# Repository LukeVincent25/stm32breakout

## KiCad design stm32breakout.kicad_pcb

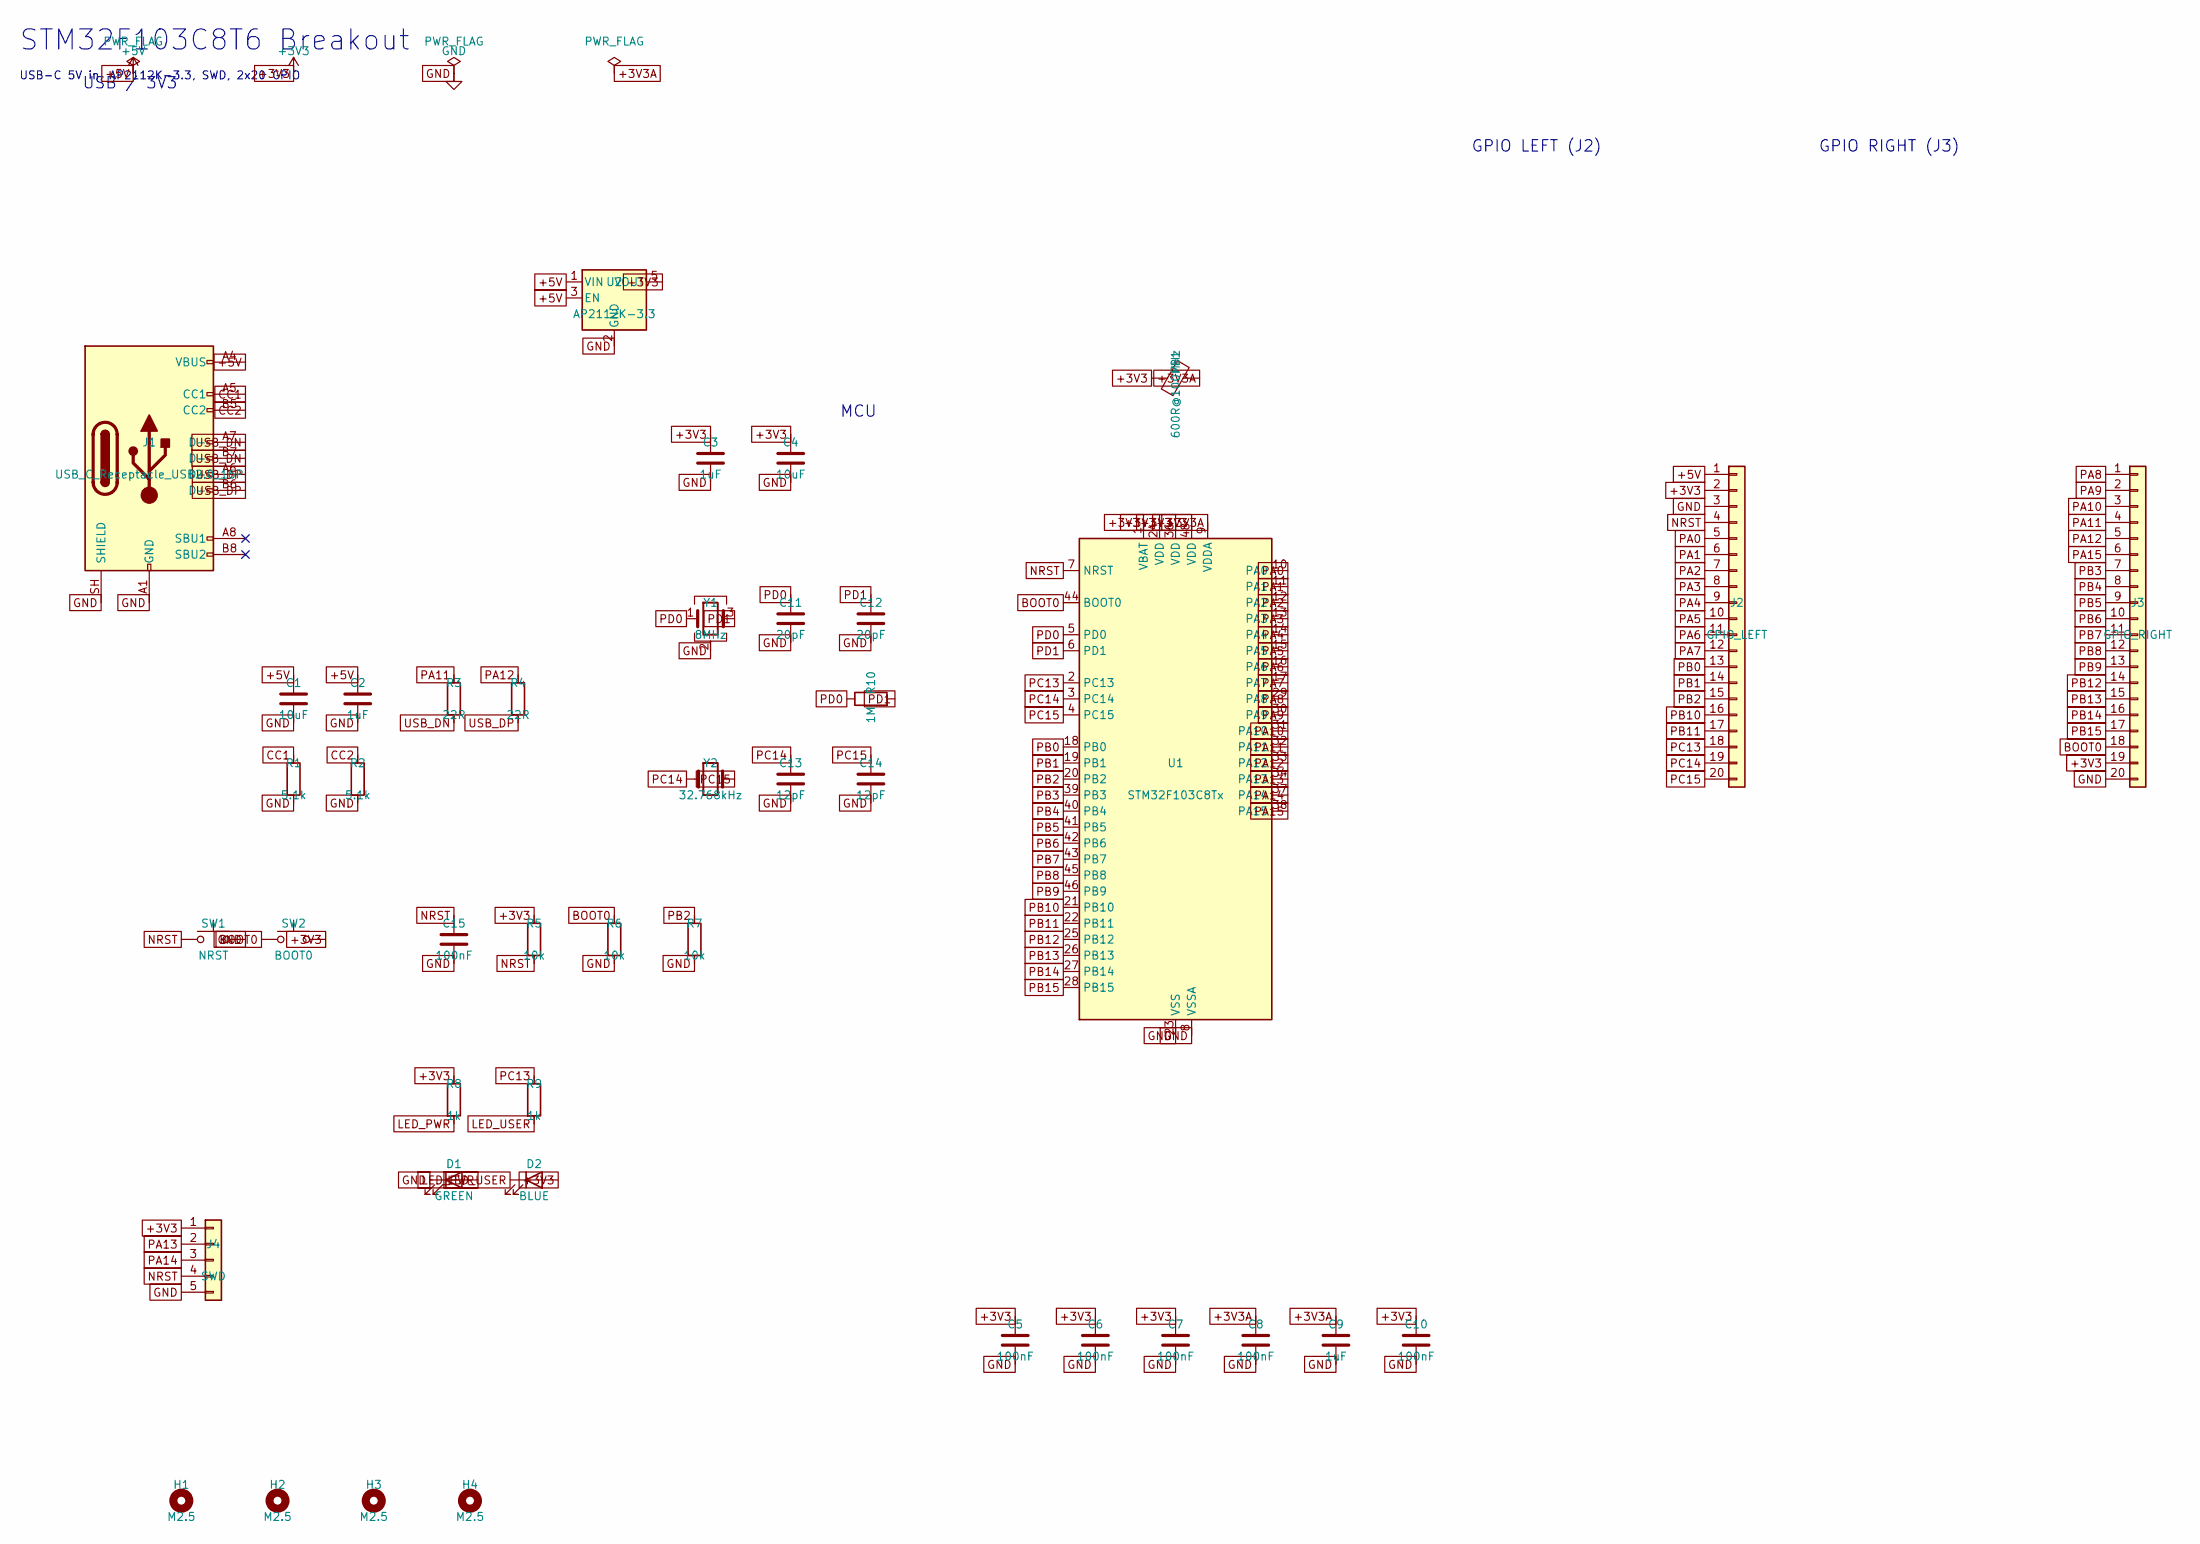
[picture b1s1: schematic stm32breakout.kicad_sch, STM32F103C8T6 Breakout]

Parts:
C1, C4: 10uF; C_0805_2012Metric; LCSC C19702
C2, C3, C9: 1uF; C_0603_1608Metric; LCSC C15849
C5, C6, C7, C8, C10, C15: 100nF; C_0603_1608Metric; LCSC C14663
C11, C12: 20pF; C_0603_1608Metric; LCSC C1645
C13, C14: 12pF; C_0603_1608Metric; LCSC C1647
D1: GREEN; LED_0603_1608Metric; LCSC C72043
D2: BLUE; LED_0603_1608Metric; LCSC C72041
FB1: 600R@100MHz; L_0603_1608Metric; LCSC C23611
H1, H2, H3, H4: M2.5; MountingHole_2.7mm_M2.5
J1: USB_C_Receptacle_USB2.0_16P; USB_C_Receptacle_HRO_TYPE-C-31-M-12; LCSC C165948
J2: GPIO_LEFT; PinHeader_1x20_P2.54mm_Vertical; LCSC C124378
J3: GPIO_RIGHT; PinHeader_1x20_P2.54mm_Vertical; LCSC C124378
J4: SWD; PinHeader_1x05_P2.54mm_Vertical; LCSC C124376
R1, R2: 5.1k; R_0603_1608Metric; LCSC C23181
R3, R4: 22R; R_0603_1608Metric; LCSC C17561
R5, R6, R7: 10k; R_0603_1608Metric; LCSC C25804
R8, R9: 1k; R_0603_1608Metric; LCSC C21190
R10: 1M; R_0603_1608Metric; LCSC C25803
SW1: NRST; SW_SPST_TL3342; LCSC C318884
SW2: BOOT0; SW_SPST_TL3342; LCSC C318884
U1: STM32F103C8Tx; LQFP-48_7x7mm_P0.5mm; LCSC C8734
U2: AP2112K-3.3; SOT-23-5; LCSC C51118
Y1: 8MHz; Crystal_SMD_3225-4Pin_3.2x2.5mm; LCSC C9002
Y2: 32.768kHz; Crystal_SMD_3215-2Pin_3.2x1.5mm; LCSC C32346

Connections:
+3V3: C3.1, C4.1, C5.1, C6.1, C7.1, C10.1, D2.2 (A), FB1.1, J2.2, J3.19, J4.1, R5.1, R8.1, SW2.2, U1.1 (VBAT), U1.24 (VDD), U1.36 (VDD), U1.48 (VDD), U2.5 (VOUT)
+3V3A: C8.1, C9.1, FB1.2, U1.9 (VDDA)
+5V: C1.1, C2.1, J1.A4 (VBUS), J1.A9 (VBUS), J1.B4 (VBUS), J1.B9 (VBUS), J2.1, U2.1 (VIN), U2.3 (EN)
BOOT0: J3.18, R6.1, SW2.1, U1.44 (BOOT0)
CC1: J1.A5 (CC1), R1.1
CC2: J1.B5 (CC2), R2.1
GND: C1.2, C2.2, C3.2, C4.2, C5.2, C6.2, C7.2, C8.2, C9.2, C10.2, C11.2, C12.2, C13.2, C14.2, C15.2, D1.1 (K), J1.A1 (GND), J1.A12 (GND), J1.B1 (GND), J1.B12 (GND), J1.SH (SHIELD), J2.3, J3.20, J4.5, R1.2, R2.2, R6.2, R7.2, SW1.2, U1.8 (VSSA), U1.23 (VSS), U1.35 (VSS), U1.47 (VSS), U2.2 (GND), Y1.2 (G), Y1.4 (G)
LED_PWR: D1.2 (A), R8.2
LED_USER: D2.1 (K), R9.2
NRST: C15.1, J2.4, J4.4, R5.2, SW1.1, U1.7 (NRST)
PA0: J2.5, U1.10 (PA0)
PA1: J2.6, U1.11 (PA1)
PA2: J2.7, U1.12 (PA2)
PA3: J2.8, U1.13 (PA3)
PA4: J2.9, U1.14 (PA4)
PA5: J2.10, U1.15 (PA5)
PA6: J2.11, U1.16 (PA6)
PA7: J2.12, U1.17 (PA7)
PA8: J3.1, U1.29 (PA8)
PA9: J3.2, U1.30 (PA9)
PA10: J3.3, U1.31 (PA10)
PA11: J3.4, R3.1, U1.32 (PA11)
PA12: J3.5, R4.1, U1.33 (PA12)
PA13: J4.2, U1.34 (PA13)
PA14: J4.3, U1.37 (PA14)
PA15: J3.6, U1.38 (PA15)
PB0: J2.13, U1.18 (PB0)
PB1: J2.14, U1.19 (PB1)
PB2: J2.15, R7.1, U1.20 (PB2)
PB3: J3.7, U1.39 (PB3)
PB4: J3.8, U1.40 (PB4)
PB5: J3.9, U1.41 (PB5)
PB6: J3.10, U1.42 (PB6)
PB7: J3.11, U1.43 (PB7)
PB8: J3.12, U1.45 (PB8)
PB9: J3.13, U1.46 (PB9)
PB10: J2.16, U1.21 (PB10)
PB11: J2.17, U1.22 (PB11)
PB12: J3.14, U1.25 (PB12)
PB13: J3.15, U1.26 (PB13)
PB14: J3.16, U1.27 (PB14)
PB15: J3.17, U1.28 (PB15)
PC13: J2.18, R9.1, U1.2 (PC13)
PC14: C13.1, J2.19, U1.3 (PC14), Y2.1
PC15: C14.1, J2.20, U1.4 (PC15), Y2.2
PD0: C11.1, R10.1, U1.5 (PD0), Y1.1
PD1: C12.1, R10.2, U1.6 (PD1), Y1.3
USB_DN: J1.A7 (D-), J1.B7 (D-), R3.2
USB_DP: J1.A6 (D+), J1.B6 (D+), R4.2

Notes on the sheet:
STM32F103C8T6 Breakout
USB-C 5V in, AP2112K-3.3, SWD, 2x20 GPIO
USB / 3V3
MCU
GPIO LEFT (J2)
GPIO RIGHT (J3)

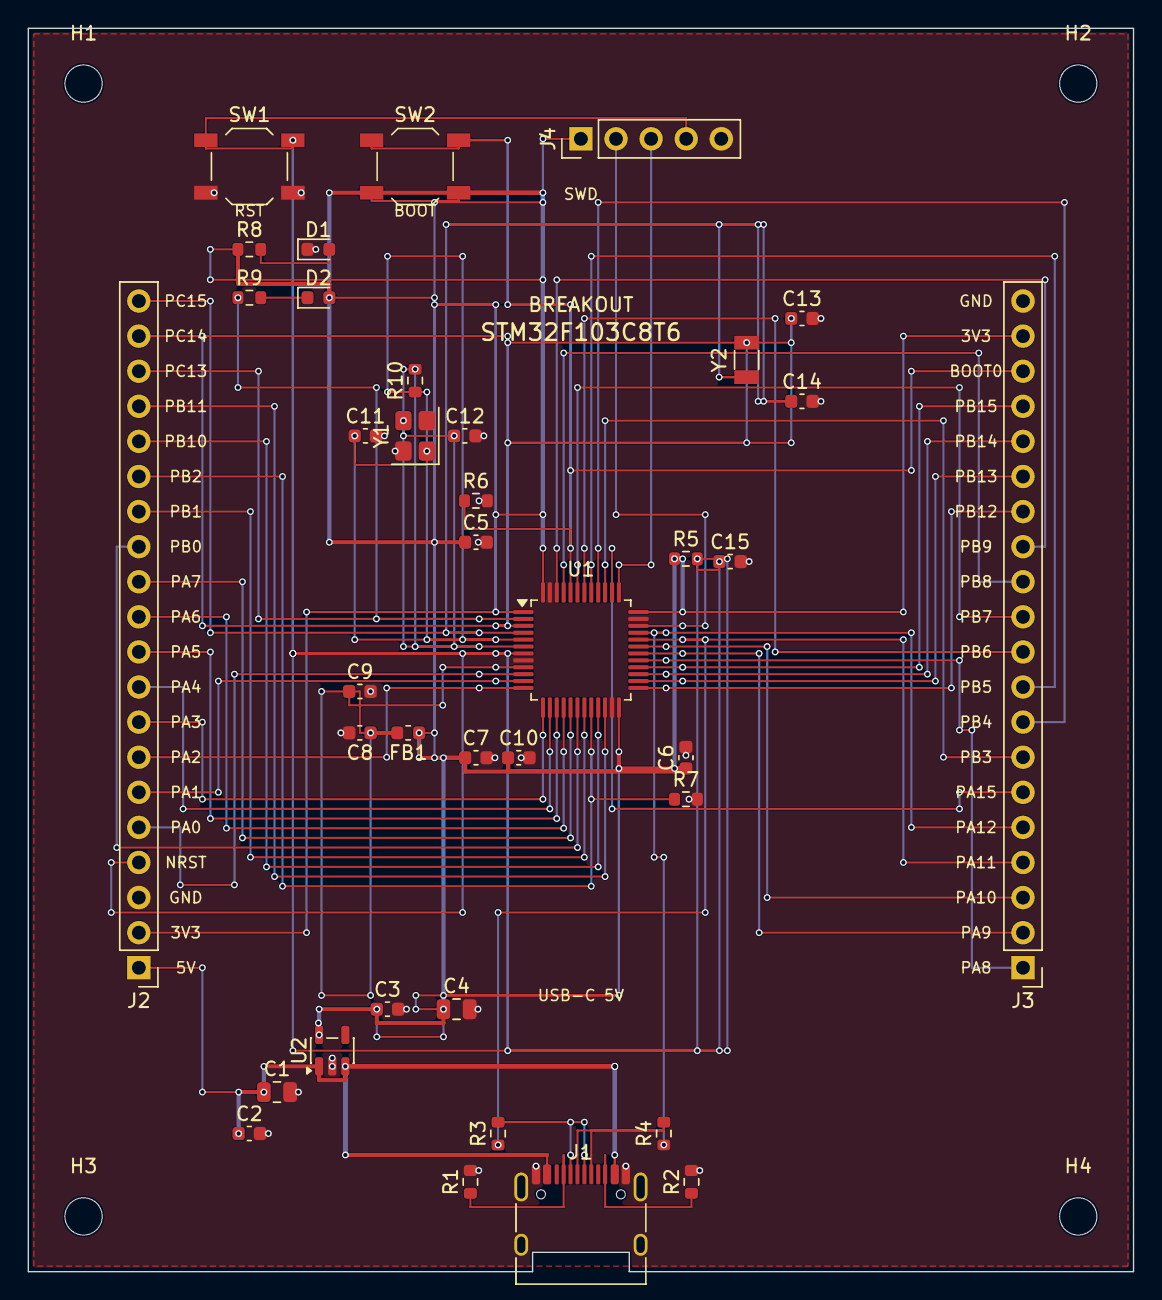
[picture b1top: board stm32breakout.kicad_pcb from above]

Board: 2 copper layers, 80.0 x 90.0 mm, 42 parts (0 on the bottom side), 49 nets.

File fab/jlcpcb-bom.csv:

Comment,Designator,Footprint,LCSC
10uF,C1,C_0805_2012Metric,C19702
1uF,C2,C_0603_1608Metric,C15849
1uF,C3,C_0603_1608Metric,C15849
10uF,C4,C_0805_2012Metric,C19702
100nF,C5,C_0603_1608Metric,C14663
100nF,C6,C_0603_1608Metric,C14663
100nF,C7,C_0603_1608Metric,C14663
100nF,C8,C_0603_1608Metric,C14663
1uF,C9,C_0603_1608Metric,C15849
100nF,C10,C_0603_1608Metric,C14663
20pF,C11,C_0603_1608Metric,C1645
20pF,C12,C_0603_1608Metric,C1645
12pF,C13,C_0603_1608Metric,C1647
12pF,C14,C_0603_1608Metric,C1647
100nF,C15,C_0603_1608Metric,C14663
GREEN,D1,LED_0603_1608Metric,C72043
BLUE,D2,LED_0603_1608Metric,C72041
600R@100MHz,FB1,L_0603_1608Metric,C23611
USB_C_Receptacle_USB2.0_16P,J1,USB_C_Receptacle_HRO_TYPE-C-31-M-12,C165948
GPIO_LEFT,J2,PinHeader_1x20_P2.54mm_Vertical,C124378
GPIO_RIGHT,J3,PinHeader_1x20_P2.54mm_Vertical,C124378
SWD,J4,PinHeader_1x05_P2.54mm_Vertical,C124376
5.1k,R1,R_0603_1608Metric,C23181
5.1k,R2,R_0603_1608Metric,C23181
22R,R3,R_0603_1608Metric,C17561
22R,R4,R_0603_1608Metric,C17561
10k,R5,R_0603_1608Metric,C25804
10k,R6,R_0603_1608Metric,C25804
10k,R7,R_0603_1608Metric,C25804
1k,R8,R_0603_1608Metric,C21190
1k,R9,R_0603_1608Metric,C21190
1M,R10,R_0603_1608Metric,C25803
NRST,SW1,SW_SPST_TL3342,C318884
BOOT0,SW2,SW_SPST_TL3342,C318884
STM32F103C8Tx,U1,LQFP-48_7x7mm_P0.5mm,C8734
AP2112K-3.3,U2,SOT-23-5,C51118
8MHz,Y1,Crystal_SMD_3225-4Pin_3.2x2.5mm,C9002
32.768kHz,Y2,Crystal_SMD_3215-2Pin_3.2x1.5mm,C32346

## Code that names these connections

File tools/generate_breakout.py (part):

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    dict(ref="U1", lib="MCU_ST_STM32F1", name="STM32F103C8Tx", value="STM32F103C8Tx",
         fp="Package_QFP:LQFP-48_7x7mm_P0.5mm", sch=(165.1, 114.3, 0), pcb=(30.0, 40.0, 0),
         pins={
             "1": "+3V3", "2": "PC13", "3": "PC14", "4": "PC15", "5": "PD0", "6": "PD1",
             "7": "NRST", "8": "GND", "9": "+3V3A", "10": "PA0", "11": "PA1", "12": "PA2",
             "13": "PA3", "14": "PA4", "15": "PA5", "16": "PA6", "17": "PA7", "18": "PB0",
             "19": "PB1", "20": "PB2", "21": "PB10", "22": "PB11", "23": "GND", "24": "+3V3",
             "25": "PB12", "26": "PB13", "27": "PB14", "28": "PB15", "29": "PA8", "30": "PA9",
             "31": "PA10", "32": "PA11", "33": "PA12", "34": "PA13", "35": "GND", "36": "+3V3",
             "37": "PA14", "38": "PA15", "39": "PB3", "40": "PB4", "41": "PB5", "42": "PB6",
             "43": "PB7", "44": "BOOT0", "45": "PB8", "46": "PB9", "47": "GND", "48": "+3V3",
         }),
    dict(ref="U2", lib="Regulator_Linear", name="AP2112K-3.3", value="AP2112K-3.3",
         fp="Package_TO_SOT_SMD:SOT-23-5", sch=(63.5, 43.18, 0), pcb=(16.0, 66.0, 90),
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         fp="Connector_PinHeader_2.54mm:PinHeader_1x20_P2.54mm_Vertical",
         sch=(266.70, 50.8, 0), pcb=(8.0, 58.0, 0),
         pins={
             "1": "+5V", "2": "+3V3", "3": "GND", "4": "NRST", "5": "PA0", "6": "PA1",
             "7": "PA2", "8": "PA3", "9": "PA4", "10": "PA5", "11": "PA6", "12": "PA7",
             "13": "PB0", "14": "PB1", "15": "PB2", "16": "PB10", "17": "PB11", "18": "PC13",
             "19": "PC14", "20": "PC15",
         }),
    dict(ref="J3", lib="Connector_Generic", name="Conn_01x20", value="GPIO_RIGHT",
         fp="Connector_PinHeader_2.54mm:PinHeader_1x20_P2.54mm_Vertical",
         sch=(320.04, 50.8, 0), pcb=(52.0, 58.0, 0),
         pins={
             "1": "PA8", "2": "PA9", "3": "PA10", "4": "PA11", "5": "PA12", "6": "PA15",
             "7": "PB3", "8": "PB4", "9": "PB5", "10": "PB6", "11": "PB7", "12": "PB8",
             "13": "PB9", "14": "PB12", "15": "PB13", "16": "PB14", "17": "PB15", "18": "BOOT0",
             "19": "+3V3", "20": "GND",
         }),
    dict(ref="J4", lib="Connector_Generic", name="Conn_01x05", value="SWD",
         fp="Connector_PinHeader_2.54mm:PinHeader_1x05_P2.54mm_Vertical",
         sch=(63.5, 165.1, 0), pcb=(24.92, 6.0, 90),
         pins={"1": "+3V3", "2": "PA13", "3": "PA14", "4": "NRST", "5": "GND"}),
    dict(ref="Y1", lib="Device", name="Crystal_GND24", value="8MHz",
         fp="Crystal:Crystal_SMD_3225-4Pin_3.2x2.5mm", sch=(114.3, 63.5, 0), pcb=(18.5, 40.0, 90),
         pins={"1": "PD0", "2": "GND", "3": "PD1", "4": "GND"}),
    dict(ref="Y2", lib="Device", name="Crystal", value="32.768kHz",
         fp="Crystal:Crystal_SMD_3215-2Pin_3.2x1.5mm", sch=(114.3, 88.9, 0), pcb=(18.5, 48.0, 90),
         pins={"1": "PC14", "2": "PC15"}),
    dict(ref="FB1", lib="Device", name="FerriteBead", value="600R@100MHz",
         fp="Inductor_SMD:L_0603_1608Metric", sch=(165.1, 48.26, 90), pcb=(30.0, 48.5, 0),
         pins={"1": "+3V3", "2": "+3V3A"}),
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         pins={"1": "+3V3", "2": "GND"}),
    dict(ref="C11", lib="Device", name="C", value="20pF",
         fp="Capacitor_SMD:C_0603_1608Metric", sch=(114.3, 76.2, 0), pcb=(18.5, 36.5, 0),
         pins={"1": "PD0", "2": "GND"}),
    dict(ref="C12", lib="Device", name="C", value="20pF",
         fp="Capacitor_SMD:C_0603_1608Metric", sch=(127.0, 76.2, 0), pcb=(18.5, 43.5, 0),
         pins={"1": "PD1", "2": "GND"}),
    dict(ref="C13", lib="Device", name="C", value="12pF",
         fp="Capacitor_SMD:C_0603_1608Metric", sch=(114.3, 101.6, 0), pcb=(18.5, 51.5, 0),
         pins={"1": "PC14", "2": "GND"}),
    dict(ref="C14", lib="Device", name="C", value="12pF",
         fp="Capacitor_SMD:C_0603_1608Metric", sch=(127.0, 101.6, 0), pcb=(18.5, 53.5, 0),
         pins={"1": "PC15", "2": "GND"}),
    dict(ref="C15", lib="Device", name="C", value="100nF",
         fp="Capacitor_SMD:C_0603_1608Metric", sch=(88.9, 114.3, 0), pcb=(40.0, 52.0, 0),
         pins={"1": "NRST", "2": "GND"}),
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         pins={"1": "CC2", "2": "GND"}),
    dict(ref="R3", lib="Device", name="R", value="22R",
         fp="Resistor_SMD:R_0603_1608Metric", sch=(63.5, 101.6, 0), pcb=(27.0, 72.0, 90),
         pins={"1": "PA11", "2": "USB_DN"}),
    dict(ref="R4", lib="Device", name="R", value="22R",
         fp="Resistor_SMD:R_0603_1608Metric", sch=(73.66, 101.6, 0), pcb=(33.0, 72.0, 90),
         pins={"1": "PA12", "2": "USB_DP"}),
    dict(ref="R5", lib="Device", name="R", value="10k",
         fp="Resistor_SMD:R_0603_1608Metric", sch=(88.9, 101.6, 0), pcb=(40.0, 55.0, 0),
         pins={"1": "+3V3", "2": "NRST"}),
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         pins={"1": "BOOT0", "2": "GND"}),
    dict(ref="R7", lib="Device", name="R", value="10k",
         fp="Resistor_SMD:R_0603_1608Metric", sch=(101.6, 114.3, 0), pcb=(22.0, 32.0, 0),
         pins={"1": "PB2", "2": "GND"}),
    dict(ref="R8", lib="Device", name="R", value="1k",
         fp="Resistor_SMD:R_0603_1608Metric", sch=(88.9, 139.7, 0), pcb=(42.0, 68.0, 0),
         pins={"1": "+3V3", "2": "LED_PWR"}),
    dict(ref="R9", lib="Device", name="R", value="1k",
         fp="Resistor_SMD:R_0603_1608Metric", sch=(101.6, 139.7, 0), pcb=(42.0, 64.0, 0),
         pins={"1": "PC13", "2": "LED_USER"}),
    dict(ref="R10", lib="Device", name="R", value="1M",
         fp="Resistor_SMD:R_0603_1608Metric", sch=(139.7, 63.5, 0), pcb=(15.0, 40.0, 90),
         pins={"1": "PD0", "2": "PD1"}),
    dict(ref="D1", lib="Device", name="LED", value="GREEN",
         fp="LED_SMD:LED_0603_1608Metric", sch=(88.9, 152.4, 0), pcb=(46.0, 68.0, 0),
         pins={"1": "GND", "2": "LED_PWR"}),
    dict(ref="D2", lib="Device", name="LED", value="BLUE",
         fp="LED_SMD:LED_0603_1608Metric", sch=(101.6, 152.4, 0), pcb=(46.0, 64.0, 0),
         pins={"1": "LED_USER", "2": "+3V3"}),
    dict(ref="SW1", lib="Switch", name="SW_Push", value="NRST",
         fp="Button_Switch_SMD:SW_SPST_TL3342", sch=(50.8, 139.7, 0), pcb=(42.0, 66.0, 0),
         pins={"1": "NRST", "2": "GND"}),
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		(rev "1")
		(company "")
		(comment 1 "USB-C PD sink (5.1k CC), 3.3V LDO, 8MHz HSE, 32.768kHz LSE")
		(comment 2 "SWD 1x5, dual 1x20 GPIO headers, BOOT0/NRST, user LED on PC13")
	)
	(lib_symbols
{chr(10).join(lib_blocks)}
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    add_silk_text(board, "BOOT", 28, 13.2, 0.8)

    # Header pin names on silk
    j2_names = ["5V","3V3","GND","NRST","PA0","PA1","PA2","PA3","PA4","PA5",
                "PA6","PA7","PB0","PB1","PB2","PB10","PB11","PC13","PC14","PC15"]
    j3_names = ["PA8","PA9","PA10","PA11","PA12","PA15","PB3","PB4","PB5","PB6",
                "PB7","PB8","PB9","PB12","PB13","PB14","PB15","BOOT0","3V3","GND"]
    j2 = footprints["J2"]
    for pad in j2.Pads():
        if not pad.GetNumber().isdigit():
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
